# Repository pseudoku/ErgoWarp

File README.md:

# ErgoWarp
Design Log and Code Repo for ''''Customizable'''' Split Keyboard

# **Still under construction, expect a lot of idiotic word salad and grammatical errors**

## Index
* [Introduction](#introduction)
* [Design Goals](#design-goals)
* [Design Justifications](#design-justifications)
  * [Row Placement](#row-placement)
  * [Column Placement](#column-design)
  * [Compact Switches](#compact-switches)
  * [Thumb Cluster Design](#thumb-cluster-design)
  * [Palm Rest Design](#palm-rest-design)
  * [Tracking Device Design](#tracking-device--incomplete-)
* [Alternate Layout](#alternate-layout-warpman)

## Introduction

Thanks to this ever-growing and enthusiastic community, there are several options for [split scooped keyboard designs](https://github.com/BenRoe/awesome-mechanical-keyboard) and if you are willing to put some effort into printing and building a pair, you can have your very own as well. However, once I began to play around with them, they seemed to create more problems than they solved -

1. The typing experience of the thumb cluster and pinkie columns improved, but still felt awkward at times;
2. The necessity of still moving my wrists in order to access the inner index columns;
3. Why not design the key orientation and contour radius to suit the motion of the fingers?

And so on. I could no longer justify myself suffering physically from the designs of kind and knowledgeable, but intangible netizens smug with their take on this modern torturing device. I want in on the smugness quotas, too - and so began my financial woe and mental suffering...and here you are, dredging up this repo page somehow.

Before I exhaust your waning attention span, I will attempt to describe my concepts and experiences of this process in a level of detail you never asked for.

Glory to Datahand and Tron, our ergo forefathers.

## Design Goals
* Customizable parametric key placement
* Minimize finger movement
* Dense and comfortable thumb cluster
* Built-in ~~adjustable~~ palm rest
* Adjustable tenting
* Tracking device

## Design Justifications

### Row Placement
**Mapping finger flexion to a placement function:**
 To achieve a minimum finger movement, a more aggressive row-wise contour is desirable. Let us define two arcs of a finger tip during flexion - 
 
 1. inner (distal and intermediate flexion), and
 2. outer (distal, intermediate, and proximal flexion)
 
 ...with palm side of metacarpal phalangeal joint as the origin.
 
 These arcs are mapped to a parametric functions defining the radius of an arc at a given angle from origin with 0° as neutral full extension and 90° as full flexion. They simulate trigger motion and grab motion respectively and it is assumed that optimal row placements of keys reside somewhere between two such functions.

 Using a CAD program, I devised the following _ad hoc_ rules that will accommodate switches in the arcs.

* Define R0 as a natural trigger, oriented tangentially to the inner arc at θ= ~90° to simulate full flexion. Switch origin is offset to the top of MX switch housing.
* Define R2 as a natural tap, oriented normal to the outer arc at θ= ~60°. Switch origin is bottom of the MX switch housing.
* Define R1 as a neutral position that reside between above mentioned positions based on the following rules. Switch origin is bottom of the MX switch housing.
  * Define secondary origin, an intermediate joint of a finger at natural full extension θ= 0°
  * An angle bisected by vectors pointing to the secondary origin R0 and R2 position.
  * Intersection of bisected vector and the outer path and key orientated normal to the path.
* Define R3 as a mirrored of R1 vector across R2. Switch origin is bottom of the MX switch housing.

#### Additional parameters

**path radius offset:** for shorter fingers (ring and pinkie for me), switches origin must be offset to accommodate the switch and keycaps to avoid collision.  

**roll angle:** When I fold my fingers, the fingertips neither stay parallel nor in-plane with respect to the vector spanned by proximal phalanx and metacarpal. This deviation becomes noticeable with high contour column and column origin transformation does not correct it. (such as adding yaw - see below section). Therefore, roll transformation was added to reorient switches out of columnar plane to bring key orientation closer to natural path of finger tips.

### Column Design
Each origins of columns defined above can be transformed to fit the natural spread and orientation of fingers. For better (ergonomically) or worse (design complexity), we can loosen the orthogonality restriction between columns and gain the freedom to yaw and roll the columns to conform to the arch of palm. With the traditional MX switch and keycap, the out of plane features collide with adjacent columns when optimized for correct placement. Without desperate measures, as we will discuss later, the compromised placement with a high contour leads to a typing experience that was subpar at best, given my finger length and spread. Major issue was that the outer most keys such as outer index and pinkie top rows required wrist motion and exaggerated extensions to hit the keys. This may not be the case for those with longer fingers and requires inputs from those who is willing to try this design.

Notes on some of the observations made during the design iteration on each columns without applying compact switches.
* Column 0: (Ternary Index) though feasible, difficult to press and infrequently used key set recommended (see Prototype 1) R0 is somewhat accessible, if you must.
* Column 1: (Secondary Index) Rolled by 20°, at this angle R0 caps (DSA) corner must be shaved.
* Column 2: (Primary Index)  not rolled, though ideally 15° is desirable, but it would collide with C3. There is also natural yaw of ~12°, but in order to accommodate C0 & C1 it is ignored.
* Column 3: (Middle) 9° roll. ideally more is desirable.   
* Column 4: (Ring) 12° switch roll. ~10° yaw is desirable.  
* Column 5: (Pinky) neutral position has great enough yaw ~42° to split the column from the rest, as observed in top view.
 column without aggressive yaw was tested, but the result required continual effort to keep finger on columns.
* Column 6: (Secondary Pinky) R0 and R1 is good candidate. It's an attractive option if you wish to support such tradition rather than using the thumb cluster.  

### Compact Switches

My initial intention of this project was to keep the design accessible by limiting it to commercially-available switches and keycaps. I did not wish to invest time redesigning key profiles; however, what was available no longer sufficed to the requirements - a narrower design, something along the lines of [alps SKCM compact](https://www.desthority.com), was needed. These are *not readily available* in large quantities, and the keycaps all the more so. 

In desperation, I resorted to lopping off the LED compartment of MX switches as well as a few keycaps to test their feasibility. The result was not pleasing to say the least, but it allowed optimization. Not entirely enthralled, but a few test prints proved that the pros out weighed the cons.

#### Cons
* Produced large wobble that hinders off axis press without gluing casing together
* The switch will no longer seat flush to the plate and will tilt without additional support (PCB or glue)
* Normal clipped keycap profile are no longer viable and custom profile will be required to improve typing comfort.

#### Pros
* By clipping the switch column wise, column separation can be reduced
  * especially useful for outer columns, which reduce wrist motions and extension required.
* Allows more aggressive row contour when necessary.
  * by clipping switch row wise, extension need to actuate adjacent upper row can be reduced: pinkie home row (C5R1)
  * by clipping switch row wise, reduce off axis press for num: ring and middle num row (C3&4R3s)
* Allows more aggressive column rolling and yaw
  * more natural ring and pinkie column orientation
* Allows thumb cluster optimization (discussed next section)

Custom key caps brought some benefits as well:
* inclined tilt for upper row improves actuation motion    
* convex curvature for R0 to reduce discomfort  

Notes on column with compact switches.
* **Column 0: (Ternary Index)
* Column 1: (Secondary Index)
* Column 2: (Primary Index)  not rolled, though ideally 15° is desirable, but it would collide with C3. There is also natural yaw of ~12°, but in order to accommodate C0 & C1 it is ignored.
* Column 3: (Middle) 9° roll. ideally more is desirable.   
* Column 4: (Ring) 12° switch roll. ~10° yaw is desirable.  
* Column 5: (Pinky) neutral position has great enough yaw ~42° to split the column from the rest, as observed in top view.
 column without aggressive yaw was tested, but the result required continual effort to keep finger on columns.
* Column 6: (Secondary Pinky) R0 and R1 is good candidate. It's an attractive option if you wish to support such tradition rather than using the thumb cluster.**  

### Thumb Cluster Design
I created a stick representation of my thumb in OpenSCAD. Initial attempts sought to pack as many switches near the ideal thumb motion, without considering collision. While keys were accessible, they did not produce efficient press, and produced strain because of the thumb position. I've replicated and tested other notable design philosophies - [Datahand](https://en.wikipedia.org/wiki/DataHand), [Dactyl-Manuform](https://github.com/tshort/dactyl-keyboard), and [DMOTE](https://github.com/burabure/dmote-keyboard) - and ended up with following design criteria, in order of priority -

* **Place highest priority on thumb home. Cluster must be as close as possible to thumb neutral position and orientation.**

 Compromising with this a cardinal design sin, and it is exacerbated when the number of cluster keys increases. To accomplish this for ErgoWarp, C1R0 (secondary index bottom row) was removed and replaced with C0R1 (ternary index home row) which allowed thumb cluster to come closer to its optimal location.

 _Natural thumb position should be measured with ones hand down by one's side not at the typing position (arm out); thumb abduction will be exaggerated leading to incorrect optimization_
 
* **Prefer actuation with palm sides surface (adduction and flexion and not abduction and extension)**

  ~~Most compact split keyboards rely on 1u thumb clusters, with it We are accustomed to pressing space bar with side of the thumb, so much so that I was recreating this bad design despite given the opportunity to correct them. All three mentioned forerunners have broken out of the box albite with their choice of priorities and compromises. When press orientation becomes thumb flexion near the neutral thumb position, the use of heavy switch must be avoided, as the torque will shift wrist position which creates strain when chording with same hand fingers. DataHand breaks this design philosophy, but it is the result of adapting light low travel switch irreplicable with MX switches. manuform follows this to the t, but by reducing the priority to minimize motion. DMOTE also follows this, but prioritize cluster density over correct orientations.~~ needs edit

* **Minimize travel distance while maintaining correct press orientation**

  This also means that high concave contour designs that conforms to the key profiles should be avoided. To reiterate, avoid adapting datahand like welled cluster with MX switches; they may reduce travel somewhat, but it is in no way a comfortable design nor do they allow accurate chording. The design goal seems conflicting statement with normal MX switches, but by uti
  
* **Ability to chord press**

  It is desirable to place modifiers and layers on thumb cluster, but without the ability to chord them effectively, their utility is hampered. especially when this design takes away conventional bottom row modifiers. Utilizing super, hyper modifiers, layers and tap modifiers are well intended, but compromised solution adding mental load when good thumb cluster design can do it all. Avoiding awkward wrist position and motion when chording requires all mentioned design goals.

The result is a compact six-key design akin to DMOTE. 

The justification and description of each position is as follows - the first three are a neutral-position cluster requiring minimum movement to actuate.
1. T0 (red) - actuated by a neutral tip addution, simulating a pinching motion. it is the most comfortable press and since its motion separate, least prone to miss-press. thus it is the home key.
2. T1 (blue) - neutral tip. this can be actuated by combing distal flexion. allows fast transition from homekey and is best suited for layer or shift.
3. T2 (green) - in terms of placement this is closest to the true neutral position of thumb. By flexing or sliding the medial joint, the switch can be actuated. It is also efficient, since it allows chording between T3 and T4.

The next three are outer sets -
1. T3 (white) - adduction with flexed distal faster of outer set.
2. T4 (purple)
3. T5 (yellow)

The cylinder represents the thumb. (thumb cluster ver2)

Desirable traits for the thumb cluster -

1. Dox-like style attempt to minimize travel by having normal cluster and maintain chording to a degree, but often the thumb home is too. but problem with side adduction press is that it produce strenuous press when combine with high extension.

2. Manuform breaks the compact cluster criteria to achieve correct orientation, but doing so with normal switches produces longer travel distance and reduced efficiency on outer keys.

3. I have not tried the Datahand, but a cluster similar to such layout did not pass, mainly due to MX switches fails due to its longer actuation throws. Similarly, high concave contour was not good enough.

4. DMOTE - overall cluster press orientation is mostly correct, but chording is not ideal. Home is too far from neutral (with my thumb length) and there is high collision with the index columns. Clustering seems to be prioritized over orientation for anterior presses, and seems awkward.

With compact MX switches
 1. Narrower index columns improves thumb home position and reduces collision issue
 2. Further improve thumb home position by getting moving of bottom row on secondary index to home row ternary index     
 3. Decouple orientation and distance,
    a) minimize adjacent switch distance with out resorting to high contour
    b) correct orientation without lower collision issues

## Palm Rest Design
~~wrist rest~~
~~putting load on nerve path of hand and palm all cost and distribute the load properly.
a supporting structure that conforms to the cavity created by the natural arch of the palm.  
they are modeled by a sweep of traversing center with a ellipsoid  
a supporting structure that conforms to the cavity created by the natural arch of the palm.  
they are modeled by a sweep of traversing center with a ellipsoid. palm support alone is insufficient in my opinion as they do not distribute weight enough and not enough constraints as the hand moves and slips out of the support. an additional support were required.~~

a distorted ring that supports thumb metacarpal and it's ellipsoidal blob, but avoid index/thumb nerve channel.

a distorted ring that support pinkie metacarpal and it's ellipsoidal blob
when angle of tenting becomes sufficiently high >30 a proper support is required at edge side of the palm to discourage slippage while allowing free movement of pinkie finger.

## Tracking Device -*Incomplete*-
### Trackpoint
Prototype 1, 4, and 5 were made with Trackpoint in mind, but due to severe drifting issues I could not complete a usage test. After some input from another forerunner, to The cause of the drift was most likely due to me roughing around the module housing and poor mounting which applied constant distortion on module. TODO Repeat test

#### Trackpoint with Switch integration

An adapter for MX key stubs to trackpoint stub. compounding with navigation layer was attractive. Tried with prototypes 4 and 5. produced mushy feel and noise.

### Trackball: under construction

## Alternate Layout: Warpman

The effort map changed considerably to a point that I felt it was a valid excuse to consider my own layout. Vertical downward transitions are faster and Workman layout philosophy jived well on initial trial. With the reduced effort to actuate bottom row, allocating higher frequency letters was less of an issue. The generous thumb cluster also made sense to adopt a Maltron-like thumb layout. As a personal preference, emphasis on rolling and same-hand typing were also considered.

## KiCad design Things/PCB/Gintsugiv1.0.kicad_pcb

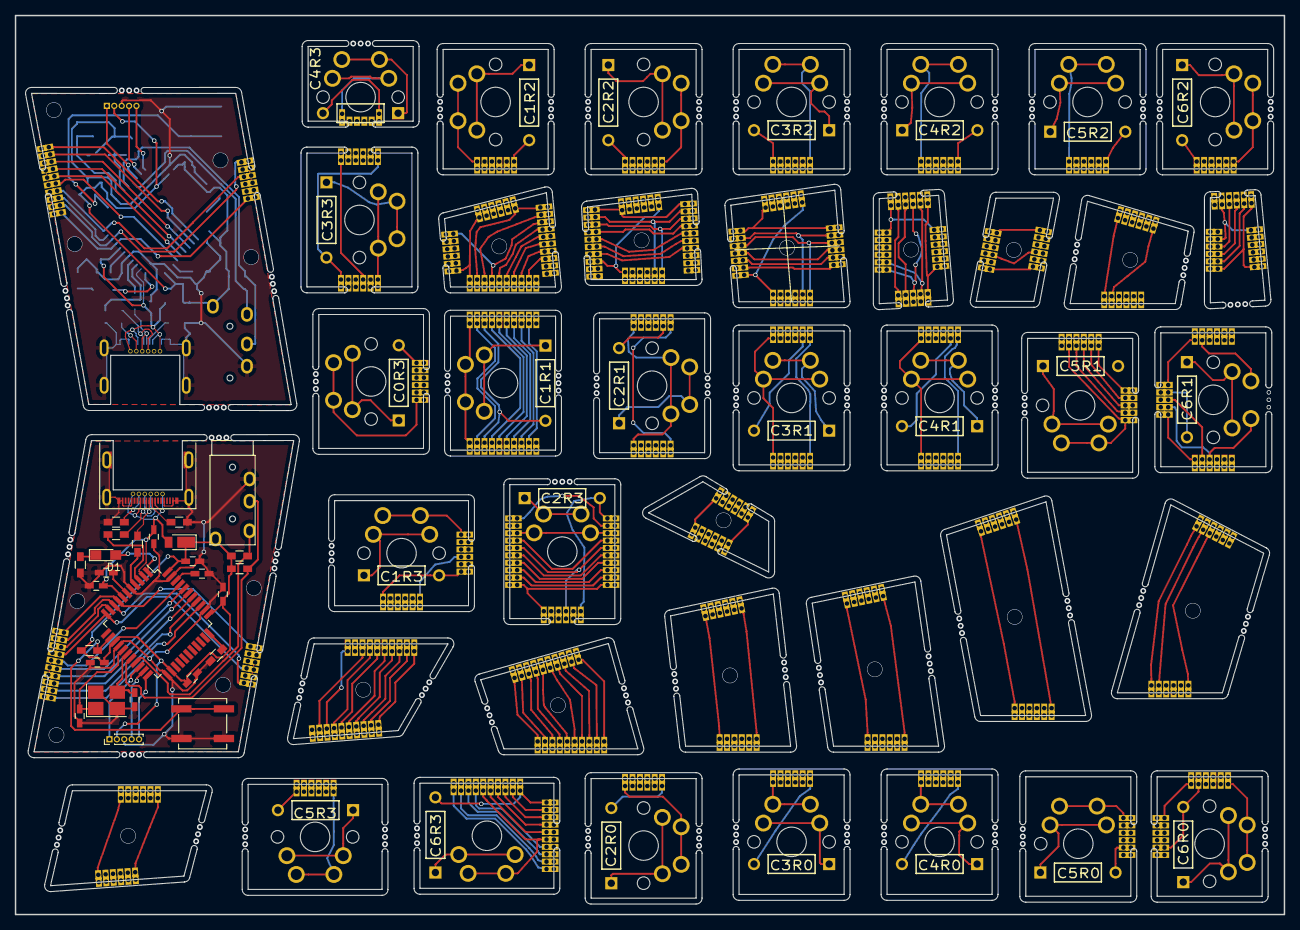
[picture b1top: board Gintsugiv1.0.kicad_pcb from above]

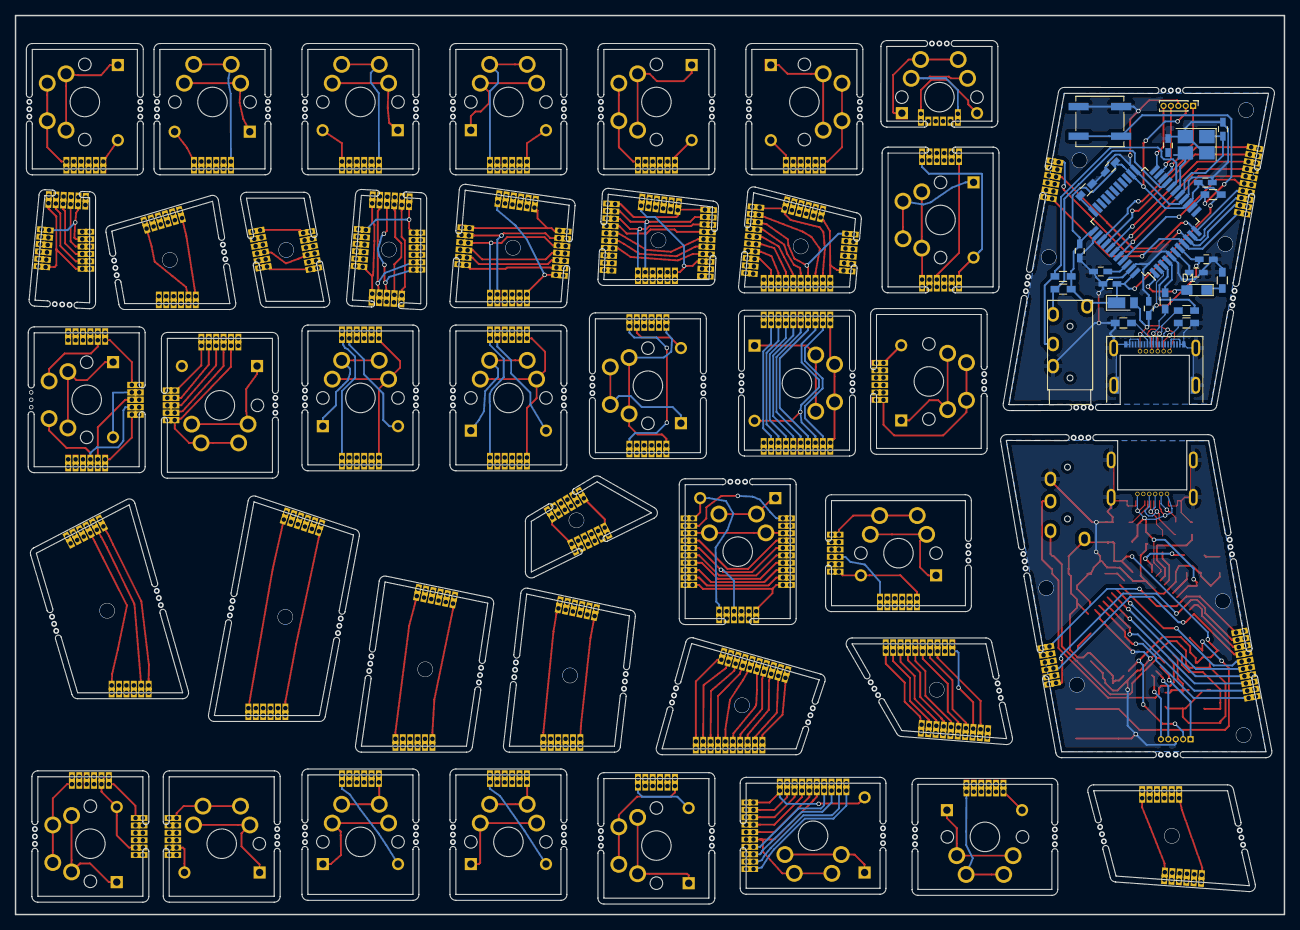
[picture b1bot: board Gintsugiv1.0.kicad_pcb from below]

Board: 2 copper layers, 171.5 x 121.5 mm, 182 parts (31 on the bottom side), 233 nets.

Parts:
B0EJ3, B0WJ3, B1EJ3, B1HJ2, B1WJ2, B1WJ3, B2BJ1, B2BJ2, B2HJ1, B2HJ2, B3BJ1, B3BJ2, B3EJ2, B3EJ3, B3EJ3#2, B3HJ1, B3HJ2, B4BJ1, B4BJ2, B4BJ3, B4HJ1, B4HJ2, B4HJ3, B4WJ2, B5BJ2, B5HJ2, B5WJ2, B6BJ1, B6BJ2, B6HJ1, B6HJ2: 1; GinConnector6
B1BJ2, B1EJ2, B2BJ3, B2EJ2, B2HJ3, B2WJ2, B3WJ3, B3WJ3#2, B5BJ3, B5HJ3: 1; GinConnector10
B3WJ2: 1; GinConnector7
B4EJ2: 1; GinConnector5
C0EJ3, C1BJ2, C1BJ3, C1EJ3, C2BJ1, C2BJ2, C2HJ0, C2HJ1, C2WJ3, C3BJ1, C3BJ2, C3EJ3, C3HJ0, C3HJ1, C3WJ3, C4BJ1, C4BJ2, C4HJ0, C4HJ1, C5BJ2, C5EJ0, C5HJ1, C5HJ3, C6BJ1, C6BJ2, C6HJ0, C6HJ1, C6WJ0: 1; GinConnector6
C0R3, C1R2, C1R3, C2R0, C2R1, C2R2, C3R0, C3R1, C3R2, C3R3, C4R0, C4R1, C4R2, C4R3, C5R2, C5R3, C6R0, C6R1, C6R2: SW_Push; CHERRY_simple
C1, C1#2, C2, C2#2, C3, C3#2, C4, C4#2, C5, C5#2, C7, C7#2: 0u1; C_0603_HandSoldering
C1BJ1, C1HJ1, C2BJ3, C2HJ3, C6EJ3, C6HJ3: 1; GinConnector10
C1R1, C2R3, C6R3: SW_Push; CHERRY_no_mount
C4WJ3: 1; GinConMin6
C5EJ1, C6WJ1: 1; GinConnector5
C5R0, C5R1: SW_Push; CHERRY_partial_mount
C6, C6#2: 4u7; C_0603_HandSoldering
C8, C8#2, C9, C9#2: 22pF; C_0603_HandSoldering
C10, C10#2: 1u; C_0603_HandSoldering
D1, D1#2: LED; LED_0805_HandSoldering
D2, D11, D12, D13, D20, D21, D22, D23, D30, D31, D32, D33, D40, D41, D42, D43, D50, D51, D52, D53, D60, D61, D62, D63: D; DIODE
D3, D3#2: D_Schottky; D_PowerDI-123
J1, J1#2: Audio-Jack-4; TRRS_PJ_320A
P0J1, P0J1#2: 1; Pin_Header_Straight_1x05_Pitch1.00mm
P1, P1#2: USB_C_Plug_USB2.0; CX70M-24P1
R1, R1#2, R2, R2#2: 1k; R_0603_HandSoldering
R3, R3#2: 10k; R_0603_HandSoldering
R4, R4#2, R5, R5#2: 22; R_0603_HandSoldering
R6, R6#2, R7, R7#2: 4.7k; R_0603_HandSoldering
R8, R8#2, R9, R9#2: 5k1; R_0603_HandSoldering
T4R1, T4R1#2: SW_Push; SW_SPST_B3SL-1002P
U1, U1#2: ATmega32U4; LQFP-44_10x10mm_Pitch0.8mm
Y1, Y1#2: 16Mhz; Crystal_SMD_SeikoEpson_FA238-4pin_3.2x2.5mm_HandSoldering

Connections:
/mcu and columns/MCU/D+: P1.A6, P1.B6, P1#2.A6, P1#2.B6, R4.1, R4#2.1
/mcu and columns/MCU/D-: P1.A7, P1.B7, P1#2.A7, P1#2.B7, R5.1, R5#2.1
/mcu and columns/MCU/MC1: B3WJ3.1, B3WJ3#2.1, U1.36, U1#2.36
/mcu and columns/MCU/MC2: B3WJ3.8, B3WJ3#2.8, U1.10, U1#2.10
/mcu and columns/MCU/MC3: B3EJ3.1, B3EJ3#2.1, B3WJ3.9, B3WJ3#2.9, U1.9, U1#2.9
/mcu and columns/MCU/MC4: B3EJ3.3, B3EJ3#2.3, B3WJ3.7, B3WJ3#2.7, U1.11, U1#2.11
/mcu and columns/MCU/MC5: B3WJ3.6, B3WJ3#2.6, U1.41, U1#2.41
/mcu and columns/MCU/MC6: B3WJ3.5, B3WJ3#2.5, U1.40, U1#2.40
/mcu and columns/MCU/MR0: B3WJ3.4, B3WJ3#2.4, U1.39, U1#2.39
/mcu and columns/MCU/MR1: B3WJ3.3, B3WJ3#2.3, U1.38, U1#2.38
/mcu and columns/MCU/MR2: B3WJ3.2, B3WJ3#2.2, U1.37, U1#2.37
/mcu and columns/MCU/MR3: B3EJ3.6, B3EJ3#2.6, B3WJ3.10, B3WJ3#2.10, U1.8, U1#2.8
/mcu and columns/MCU/SCL: J1.3, J1#2.3, R7.2, R7#2.2, U1.18, U1#2.18
/mcu and columns/MCU/SDA: J1.2, J1#2.2, R6.1, R6#2.1, U1.19, U1#2.19
/mcu and columns/MCU/VBUS: C5.1, C5#2.1, C6.1, C6#2.1, D3.2, D3#2.2, P1.A4, P1.A9, P1.B4, P1.B9, P1#2.A4, P1#2.A9, P1#2.B4, P1#2.B9, U1.2, U1.7, U1#2.2, U1#2.7
/mcu and columns/MCU/VCC: C1.1, C1#2.1, C2.1, C2#2.1, C3.1, C3#2.1, C4.1, C4#2.1, D3.1, D3#2.1, J1.1, J1#2.1, P0J1.2, P0J1#2.2, R3.2, R3#2.2, R6.2, R6#2.2, R7.1, R7#2.1, U1.14, U1.24, U1.34, U1.44, U1#2.14, U1#2.24, U1#2.34, U1#2.44
/mcu and columns/MCU/int|TX: P0J1.4, P0J1#2.4, U1.21, U1#2.21
/mcu and columns/MCU/int|clk: P0J1.5, P0J1#2.5, U1.22, U1#2.22
/mcu and columns/MCU/int|data: P0J1.1, P0J1#2.1, U1.20, U1#2.20
GND: C1.2, C1#2.2, C2.2, C2#2.2, C3.2, C3#2.2, C4.2, C4#2.2, C5.2, C5#2.2, C6.2, C6#2.2, C7.1, C7#2.1, C8.2, C8#2.2, C9.2, C9#2.2, C10.2, C10#2.2, J1.4, J1#2.4, P0J1.3, P0J1#2.3, P1.A1, P1.A12, P1.B1, P1.B12, P1.S1, P1#2.A1, P1#2.A12, P1#2.B1, P1#2.B12, P1#2.S1, R1.2, R1#2.2, R2.2, R2#2.2, R8.2, R8#2.2, R9.2, R9#2.2, T4R1.2, T4R1#2.2, U1.5, U1.15, U1.23, U1.35, U1.43, U1#2.5, U1#2.15, U1#2.23, U1#2.35, U1#2.43, Y1.2, Y1.4, Y1#2.2, Y1#2.4
unnamed: B0EJ3.1, B0WJ3.6
unnamed: B0EJ3.6, B0WJ3.1
unnamed: B1BJ2.1, B1HJ2.6, B1WJ2.6
unnamed: B1BJ2.2, B1EJ2.10, B1HJ2.1
unnamed: B1BJ2.3, B1EJ2.9
unnamed: B1BJ2.4, B1EJ2.8, B1WJ2.1
unnamed: B1BJ2.5, B1EJ2.7
unnamed: B1BJ2.6, B1EJ2.6
unnamed: B1BJ2.7, B1EJ2.5
unnamed: B1BJ2.8, B1EJ2.4
unnamed: B1BJ2.9, B1EJ2.3
unnamed: B1EJ3.1, B1WJ3.6
unnamed: B1EJ3.3, B1WJ3.4
unnamed: B1EJ3.6, B1WJ3.1
unnamed: B2BJ1.1, B2HJ1.6
unnamed: B2BJ1.6, B2HJ1.1
unnamed: B2BJ2.1, B2HJ2.1, B2WJ2.8
unnamed: B2BJ2.5, B2EJ2.9, B2WJ2.2
unnamed: B2BJ2.6, B2EJ2.8, B2WJ2.3
unnamed: B2BJ3.1, B2HJ3.10
unnamed: B2BJ3.2, B2HJ3.9
unnamed: B2BJ3.3, B2HJ3.8
unnamed: B2BJ3.4, B2HJ3.7
unnamed: B2BJ3.5, B2HJ3.6
unnamed: B2BJ3.6, B2HJ3.5
unnamed: B2BJ3.7, B2HJ3.4
unnamed: B2BJ3.8, B2HJ3.2
unnamed: B2BJ3.10, B2HJ3.3
unnamed: B2EJ2.4, B2WJ2.7
unnamed: B2EJ2.5, B2WJ2.6
unnamed: B2EJ2.6, B2WJ2.5
unnamed: B2EJ2.7, B2WJ2.4
unnamed: B2EJ2.10, B2HJ2.6, B2WJ2.1
unnamed: B3BJ1.1, B3HJ1.6
unnamed: B3BJ1.6, B3HJ1.1
unnamed: B3BJ2.1, B3HJ2.1, B3WJ2.7
unnamed: B3BJ2.5, B3EJ2.5, B3WJ2.2
unnamed: B3BJ2.6, B3EJ2.4, B3WJ2.3
unnamed: B3EJ2.1, B3WJ2.6
unnamed: B3EJ2.2, B3WJ2.5
unnamed: B3EJ2.3, B3WJ2.4
unnamed: B3EJ2.6, B3HJ2.6, B3WJ2.1
unnamed: B3EJ3.2, B3EJ3#2.2
unnamed: B3EJ3.4, B3EJ3#2.4
unnamed: B3EJ3.5, B3EJ3#2.5
unnamed: B4BJ1.1, B4HJ1.6
unnamed: B4BJ1.6, B4HJ1.1
unnamed: B4BJ2.1, B4HJ2.6, B4WJ2.6
unnamed: B4BJ2.5, B4EJ2.4, B4WJ2.2
unnamed: B4BJ2.6, B4EJ2.3, B4WJ2.3
unnamed: B4BJ3.1, B4HJ3.6
unnamed: B4BJ3.6, B4HJ3.1
unnamed: B4EJ2.1, B4WJ2.5
unnamed: B4EJ2.2, B4WJ2.4
unnamed: B4EJ2.5, B4HJ2.1, B4WJ2.1
unnamed: B5BJ2.2, B5HJ2.6, B5WJ2.5
unnamed: B5BJ2.3, B5WJ2.4
unnamed: B5BJ2.4, B5WJ2.3
unnamed: B5BJ2.5, B5WJ2.2
unnamed: B5BJ2.6, B5HJ2.1, B5WJ2.1
unnamed: B5BJ3.1, B5HJ3.10
unnamed: B5BJ3.2, B5HJ3.9
unnamed: B5BJ3.3, B5HJ3.8
unnamed: B5BJ3.4, B5HJ3.7
unnamed: B5BJ3.5, B5HJ3.6
unnamed: B5BJ3.6, B5HJ3.5
unnamed: B5BJ3.7, B5HJ3.4
unnamed: B5BJ3.8, B5HJ3.3
unnamed: B5BJ3.9, B5HJ3.2
unnamed: B5BJ3.10, B5HJ3.1
unnamed: B6BJ1.1, B6HJ1.6
unnamed: B6BJ1.2, B6HJ1.5
unnamed: B6BJ1.6, B6HJ1.4
unnamed: B6BJ2.1, B6HJ2.6
unnamed: B6BJ2.2, B6HJ2.1
unnamed: C0EJ3.1, C0R3.1
unnamed: C0EJ3.6, D2.1
unnamed: C0R3.2, D2.2
unnamed: C1BJ1.1, C1HJ1.10, C1R1.1
unnamed: C1BJ1.2, C1HJ1.9
unnamed: C1BJ1.3, C1HJ1.8, D11.1
unnamed: C1BJ1.4, C1HJ1.7
unnamed: C1BJ1.5, C1HJ1.6
unnamed: C1BJ1.6, C1HJ1.5
unnamed: C1BJ1.7, C1HJ1.4
unnamed: C1BJ1.8, C1HJ1.3
unnamed: C1BJ1.9, C1HJ1.2
unnamed: C1BJ2.1, C1R2.1
unnamed: C1BJ2.6, D12.1
unnamed: C1BJ3.1, C1EJ3.1, D13.1
unnamed: C1BJ3.6, C1EJ3.3
unnamed: C1EJ3.6, C1R3.1
unnamed: C1R1.2, D11.2
unnamed: C1R2.2, D12.2
unnamed: C1R3.2, D13.2
unnamed: C2BJ1.1, C2HJ1.6, C2R1.2
unnamed: C2BJ1.6, C2HJ1.1
unnamed: C2BJ2.1, D22.1
unnamed: C2BJ2.6, C2R2.1
unnamed: C2BJ3.1, C2HJ3.10, C2WJ3.1
unnamed: C2BJ3.2, C2HJ3.9
unnamed: C2BJ3.3, C2HJ3.8
unnamed: C2BJ3.4, C2HJ3.7
unnamed: C2BJ3.5, C2HJ3.6
unnamed: C2BJ3.6, C2HJ3.5, C2WJ3.4
unnamed: C2BJ3.7, C2HJ3.4
unnamed: C2BJ3.8, C2HJ3.3, C2R3.2
unnamed: C2BJ3.9, C2HJ3.1
unnamed: C2BJ3.10, C2WJ3.6, D23.1
unnamed: C2HJ0.1, D20.1
unnamed: C2HJ0.6, C2R0.1
unnamed: C2HJ1.2, D21.1
unnamed: C2R0.2, D20.2
unnamed: C2R1.1, D21.2
unnamed: C2R2.2, D22.2
unnamed: C2R3.1, D23.2
unnamed: C3BJ1.1, C3HJ1.6, C3R1.2
unnamed: C3BJ1.6, C3HJ1.1
unnamed: C3BJ2.1, D32.1
unnamed: C3BJ2.6, C3R2.1
unnamed: C3EJ3.1, C3WJ3.1, D33.1
unnamed: C3EJ3.6, C3WJ3.4
unnamed: C3HJ0.1, D30.1
unnamed: C3HJ0.6, C3R0.1
unnamed: C3HJ1.2, D31.1
unnamed: C3R0.2, D30.2
unnamed: C3R1.1, D31.2
unnamed: C3R2.2, D32.2
unnamed: C3R3.1, D33.2
unnamed: C3R3.2, C3WJ3.6
unnamed: C4BJ1.1, C4HJ1.6, C4R1.2
unnamed: C4BJ1.6, C4HJ1.1
unnamed: C4BJ2.1, C4R2.1
unnamed: C4BJ2.6, D42.1
unnamed: C4HJ0.1, D40.1
unnamed: C4HJ0.6, C4R0.1
unnamed: C4HJ1.2, D41.1
unnamed: C4R0.2, D40.2
unnamed: C4R1.1, D41.2
unnamed: C4R2.2, D42.2
unnamed: C4R3.1, D43.2
unnamed: C4R3.2, C4WJ3.1
unnamed: C4WJ3.6, D43.1
unnamed: C5BJ2.1, C5R2.1
unnamed: C5BJ2.6, D52.1
unnamed: C5EJ0.2, D50.1
unnamed: C5EJ0.6, C5R0.2
unnamed: C5EJ1.1, C5HJ1.5, C5R1.1
unnamed: C5EJ1.2, C5HJ1.4
unnamed: C5EJ1.3, C5HJ1.3
unnamed: C5EJ1.4, C5HJ1.2, D51.1
unnamed: C5EJ1.5, C5HJ1.1
unnamed: C5HJ3.1, C5R3.1
unnamed: C5HJ3.6, D53.1
unnamed: C5R0.1, D50.2
unnamed: C5R1.2, D51.2
unnamed: C5R2.2, D52.2
unnamed: C5R3.2, D53.2
unnamed: C6BJ1.1, C6WJ1.5
unnamed: C6BJ1.2, C6WJ1.3
unnamed: C6BJ1.3, C6HJ1.5, C6R1.1, C6WJ1.4
unnamed: C6BJ2.1, D62.1
unnamed: C6BJ2.6, C6R2.1
unnamed: C6EJ3.1, C6HJ3.10
unnamed: C6EJ3.2, C6HJ3.9
unnamed: C6EJ3.3, C6HJ3.8
unnamed: C6EJ3.4, C6HJ3.7
unnamed: C6EJ3.5, C6HJ3.6, C6R3.1
unnamed: C6EJ3.6, C6HJ3.5
unnamed: C6EJ3.7, C6HJ3.4
unnamed: C6EJ3.8, C6HJ3.3
unnamed: C6EJ3.9, C6HJ3.2
unnamed: C6EJ3.10, C6HJ3.1, D63.1
unnamed: C6HJ0.1, C6R0.1
unnamed: C6HJ0.5, C6WJ0.5, D60.1
unnamed: C6HJ0.6, C6WJ0.1
unnamed: C6HJ1.6, C6WJ1.1
unnamed: C6R0.2, D60.2
unnamed: C6R1.2, D61.2
unnamed: C6R2.2, D62.2
unnamed: C6R3.2, D63.2
unnamed: C6WJ1.2, D61.1
unnamed: C7.2, C7#2.2, U1.42, U1#2.42
unnamed: C8.1, C8#2.1, U1.16, U1#2.16, Y1.1, Y1#2.1
unnamed: C9.1, C9#2.1, U1.17, U1#2.17, Y1.3, Y1#2.3
unnamed: C10.1, C10#2.1, U1.6, U1#2.6
unnamed: D1.1, D1#2.1, R2.1, R2#2.1
unnamed: D1.2, D1#2.2, U1.1, U1#2.1
unnamed: P1.A2, P1#2.A2
unnamed: P1.A3, P1#2.A3
unnamed: P1.A5, P1#2.A5, R8.1, R8#2.1
unnamed: P1.A8, P1#2.A8
unnamed: P1.A10, P1#2.A10
unnamed: P1.A11, P1#2.A11
unnamed: P1.B2, P1#2.B2
unnamed: P1.B3, P1#2.B3
unnamed: P1.B5, P1#2.B5, R9.1, R9#2.1
unnamed: P1.B8, P1#2.B8
unnamed: P1.B10, P1#2.B10
unnamed: P1.B11, P1#2.B11
unnamed: R1.1, R1#2.1, U1.33, U1#2.33
unnamed: R3.1, R3#2.1, T4R1.1, T4R1#2.1, U1.13, U1#2.13
unnamed: R4.2, R4#2.2, U1.4, U1#2.4
unnamed: R5.2, R5#2.2, U1.3, U1#2.3
unnamed: U1.12, U1#2.12
unnamed: U1.25, U1#2.25
unnamed: U1.26, U1#2.26
unnamed: U1.27, U1#2.27
unnamed: U1.28, U1#2.28
unnamed: U1.29, U1#2.29
unnamed: U1.30, U1#2.30
unnamed: U1.31, U1#2.31
unnamed: U1.32, U1#2.32

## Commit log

2018-04-26 Update README.md
    In Progress
2018-05-03 Edit
2018-05-03 aaaa
2018-05-07 Read.Me
    Read Me and Soem OpenSCAD
2018-06-02 more variation
2018-11-18 Quick update
    cut uneeded content. upload most recent STL and SCAD files
2018-11-18 add photo
2018-11-27 Clip Switch Moddification
    Improve code legibility
    Added Flick Switch suppor
    Added Clipped Switch suppor
    Added Rortary encoder suppor
    fixed keycaps clipping at C3R1 and C4R0
2018-11-28 touch up
    hotfix on innerweb
2018-12-02 optimization and caps
    added keycaps to optimize clipped keys
    fixed web and inner web
    optimizing compact build.
2018-12-06 rev8 version update
2018-12-06 thumb optimization
    revert back to oleder style thumb position now that direction of optimization tas changed: remove C1R0 in order to place thumb in more realistic neutral position.
2018-12-07 Waaarped test build
    commit to branch. Test print model
2018-12-23 Ver9 Malformed
    ver9 malformed
    keycaps and gintsugi ver 1.0
2019-01-13 Mounting Tests
    Ball Mounts Parts
2019-01-18 hyperwarped update
    ver.2
2019-04-09 Proto Build update
    commiting to a build
2019-04-09 photo ref
    changed reference photo on readme
2022-10-07 Tidy up the "word salad"
2022-10-07 Create index links
